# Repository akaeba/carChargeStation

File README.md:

# carChargeStation
Charging station for Faller cars (Li-ion/NiMH)

## Ideas
* use [MCP1631V](https://www.microchip.com/wwwproducts/en/MCP1631V)

## References

### Datasheet
* [MCP1631V](http://ww1.microchip.com/downloads/en/DeviceDoc/22063b.pdf)

### User Guides
* [MCP1631HV Digitally Controlled Programmable Current Source Reference Design](http://ww1.microchip.com/downloads/en/DeviceDoc/51798a.pdf)

### Eval Boards
* [MCP1631RD-DCPC1](https://www.microchip.com/DevelopmentTools/ProductDetails/PartNO/MCP1631RD-DCPC1) (MCP1631HV Digitally Controlled Programmable Current Source Reference Design)

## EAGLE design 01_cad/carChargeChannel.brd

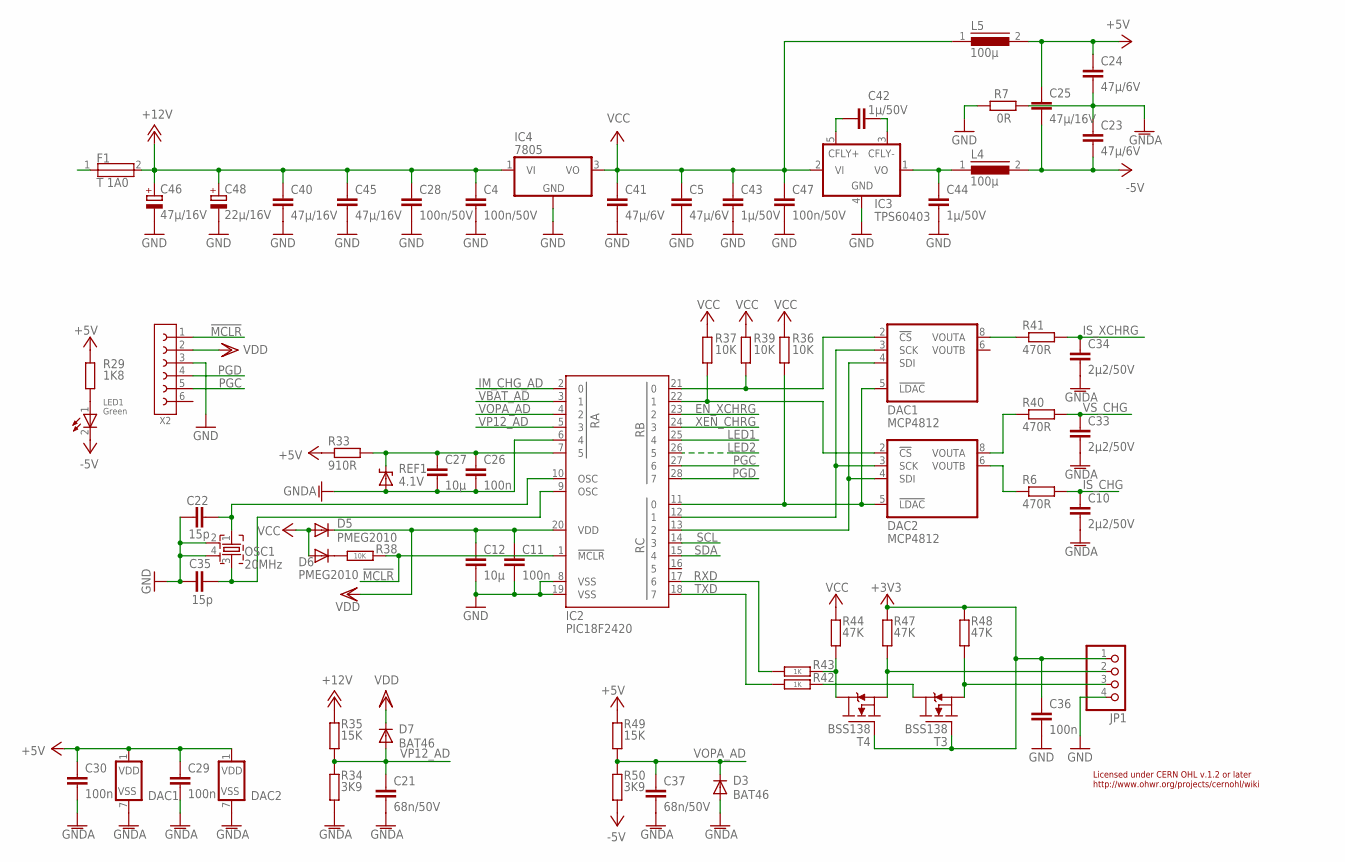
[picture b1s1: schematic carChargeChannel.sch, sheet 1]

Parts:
C4, C28, C47: 100n/50V; 1206
C5, C23, C24, C41: 47µ/6V; 1206
C10, C33, C34: 2µ2/50V; 1206
C11, C26, C29, C30, C36: 100n; 1206
C12, C27: 10µ; 1206
C21, C37: 68n/50V; 1206
C22, C35: 15p; 1206
C25, C40, C45: 47µ/16V; 1210
C42, C43, C44: 1µ/50V; 1206
C46: 47µ/16V; PANC
C48: 22µ/16V; PANB
D3, D7: BAT46; SOD123
D5, D6: PMEG2010; SOD323
DAC1, DAC2: MCP4812; MSOP8
F1: T 1A0; OMT125
IC2: PIC18F2420; SOIC28-7.62
IC3: TPS60403; SOT23-5
IC4: 7805; TO263
JP1: PINHD-1X4; 1X04
L4, L5: 100µ; 1210
LED1: Green; LED3216
OSC1: 20MHz; MT
R6, R40, R41: 470R; 1206
R7: 0R; 1206
R29: 1K8; 1206
R33: 910R; 1206
R34, R50: 3K9; 1206
R35, R49: 15K; 1206
R36, R37, R38, R39: 10K; 1206
R42, R43: 1K; 1206
R44, R47, R48: 47K; 1206
REF1: 4.1V; SOT23
T3, T4: BSS138; SOT23
X2: 2X3; BOXHD-06-2.54-S

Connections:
!CS_DAC1: DAC1.2 (!CS), IC2.21 (0), R39.1
!CS_DAC2: DAC2.2 (!CS), IC2.22 (1), R37.1
!MCLR: IC2.1 (!MCLR), R38.1, X2.1
+3V3: C36.1, JP1.1, R47.2, R48.2, T3.1 (G), T4.1 (G)
+5V: C24.1, C25.1, C29.1, C30.1, DAC1.1 (VDD), DAC2.1 (VDD), L5.2, R29.2, R33.1, R49.2; also elsewhere on the board
+12V: C4.1, C28.1, C40.1, C45.1, C46.CP (+), C48.CP (+), F1.2, IC4.1 (VI), R35.2; also elsewhere on the board
-5V: C23.2, C25.2, L4.2, LED1.2 (C), R50.1; also elsewhere on the board
EN_XCHRG: IC2.23 (2); also elsewhere on the board
GND: C4.2, C5.2, C11.2, C12.2, C22.2, C28.2, C35.2, C36.2, C40.2, C41.2, C43.2, C44.2, C45.2, C46.CN (-), C47.2, C48.CN (-), IC2.8 (VSS), IC2.19 (VSS), IC3.4 (GND), IC4.4 (GND), JP1.4, OSC1.2, OSC1.4, R7.1, X2.3; also elsewhere on the board
GNDA: C10.2, C21.2, C23.1, C24.2, C26.2, C27.2, C29.2, C30.2, C33.2, C34.2, C37.2, D3.A, DAC1.7 (VSS), DAC2.7 (VSS), IC2.6 (4), R7.2, R34.1, REF1.1 (A); also elsewhere on the board
IM_CHG_AD: IC2.2 (0); also elsewhere on the board
IS_CHG: C10.1, R6.2; also elsewhere on the board
IS_XCHRG: C34.1, R41.2; also elsewhere on the board
LED1: IC2.25 (4); also elsewhere on the board
LED2: IC2.26 (5); also elsewhere on the board
unnamed: DAC1.4 (SDI), DAC2.4 (SDI), IC2.13 (2)
unnamed: DAC1.3 (SCK), DAC2.3 (SCK), IC2.12 (1)
unnamed: C42.2, IC3.3 (CFLY-)
unnamed: C42.1, IC3.5 (CFLY+)
unnamed: DAC2.6 (VOUTB), R6.1
unnamed: DAC2.8 (VOUTA), R40.1
unnamed: DAC1.8 (VOUTA), R41.1
unnamed: C44.1, IC3.1 (VO), L4.1
unnamed: C35.1, IC2.9 (OSC), OSC1.3
unnamed: C22.1, IC2.10 (OSC), OSC1.1
unnamed: LED1.1 (A), R29.1
unnamed: DAC1.5 (!LDAC), DAC2.5 (!LDAC), IC2.11 (0), R36.1
unnamed: D6.C, R38.2
unnamed: JP1.3, R48.1, T3.2 (S)
unnamed: JP1.2, R47.1, T4.2 (S)
unnamed: R42.1, T3.3 (D)
unnamed: R43.1, R44.1, T4.3 (D)
PGC: IC2.27 (6), X2.5
PGD: IC2.28 (7), X2.4
RXD: IC2.17 (6), R43.2
SCL: IC2.14 (3)
SDA: IC2.15 (4)
TXD: IC2.18 (7), R42.2
VBAT_AD: IC2.3 (1); also elsewhere on the board
VCC: C5.1, C41.1, C43.1, C47.1, D5.A, D6.A, IC3.2 (VI), IC4.3 (VO), L5.1, R36.2, R37.2, R39.2, R44.2
VDD: C11.1, C12.1, D5.C, D7.C, IC2.20 (VDD), X2.2
VOPA_AD: C37.1, D3.C, IC2.4 (2), R49.1, R50.2
VP12_AD: C21.1, D7.A, IC2.5 (3), R34.2, R35.1
VREF_ADC: C26.1, C27.1, IC2.7 (5), R33.2, REF1.2 (C)
VS_CHG: C33.1, R40.2; also elsewhere on the board
XEN_CHRG: IC2.24 (3); also elsewhere on the board

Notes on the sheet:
Licensed under CERN OHL v.1.2 or later http://www.ohwr.org/projects/cernohl/wiki

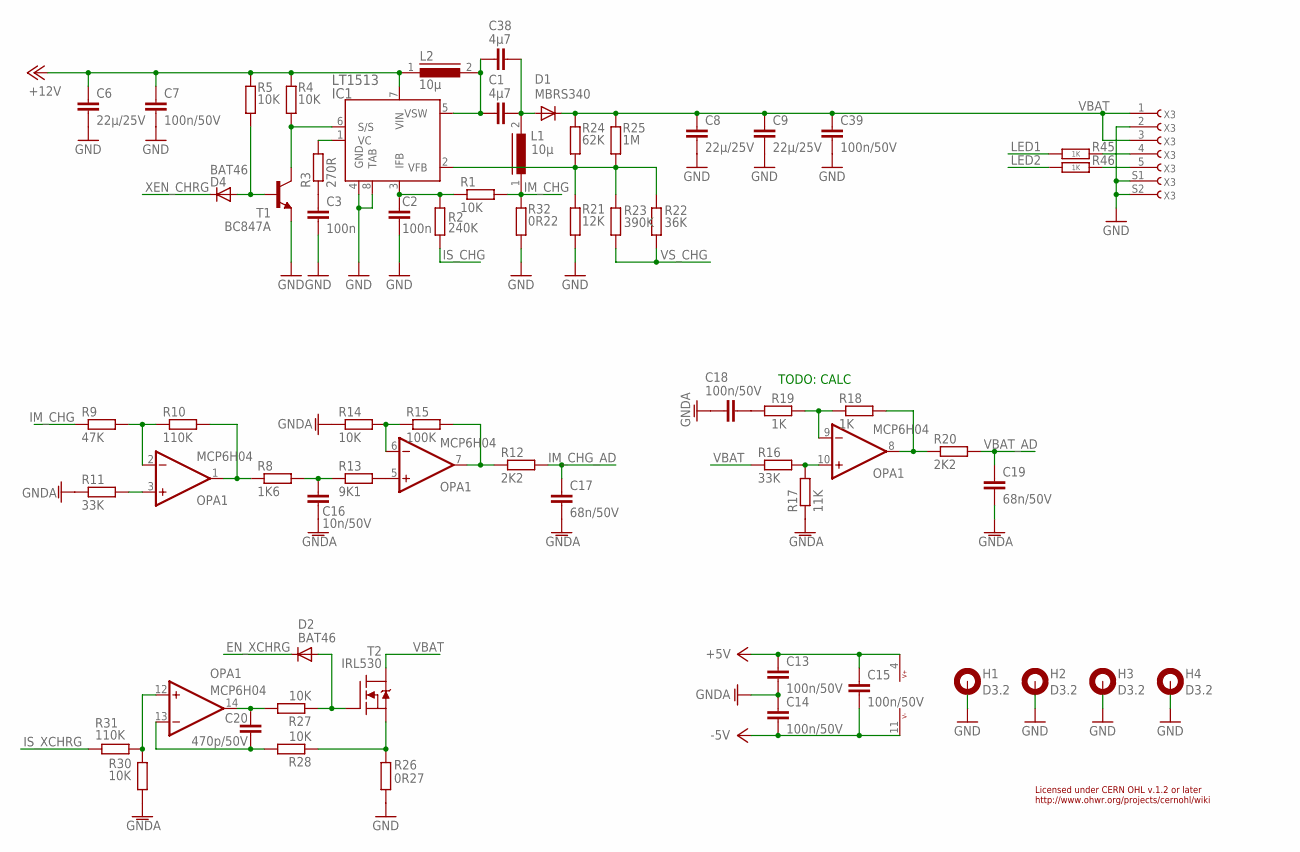
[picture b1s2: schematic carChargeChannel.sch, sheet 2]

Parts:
C1, C38: 4µ7; 1206
C2, C3: 100n; 1206
C6, C8, C9: 22µ/25V; 1210
C7, C13, C14, C15, C18, C39: 100n/50V; 1206
C16: 10n/50V; 1206
C17, C19: 68n/50V; 1206
C20: 470p/50V; 1206
D1: MBRS340; DO214AB
D2, D4: BAT46; SOD123
H1, H2, H3, H4: D3.2; 3,2-PAD
IC1: LT1513; TO263-7
L1, L2: 10µ; DR74
OPA1: MCP6H04; SOIC14
R1, R4, R5, R14, R27, R28, R30: 10K; 1206
R2: 240K; 1206
R3: 270R; 1206
R8: 1K6; 1206
R9: 47K; 1206
R10, R31: 110K; 1206
R11, R16: 33K; 1206
R12, R20: 2K2; 1206
R13: 9K1; 1206
R15: 100K; 1206
R17: 11K; 1206
R18, R19, R45, R46: 1K; 1206
R21: 12K; 1206
R22: 36K; 1206
R23: 390K; 1206
R24: 62K; 1206
R25: 1M; 1206
R26: 0R27; 1206
R32: 0R22; 1206
T1: BC847A; SOT23
T2: IRL530; TO263AB
X3: DIN5; DIN5P

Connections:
+5V: C13.1, C15.1, OPA1.4 (V+); also elsewhere on the board
+12V: C6.1, C7.1, IC1.7 (VIN), L2.1, R4.2, R5.2; also elsewhere on the board
-5V: C14.2, C15.2, OPA1.11 (V-); also elsewhere on the board
EN_XCHRG: D2.C; also elsewhere on the board
GND: C2.2, C3.2, C6.2, C7.2, C8.2, C9.2, C39.2, H1.B3,2, H2.B3,2, H3.B3,2, H4.B3,2, IC1.4 (GND), IC1.8 (TAB), R21.1, R26.1, R32.1, T1.2 (E), X3.2, X3.S1, X3.S2; also elsewhere on the board
GNDA: C13.2, C14.1, C16.2, C17.2, C18.1, C19.2, R11.1, R14.1, R17.1, R30.1; also elsewhere on the board
IM_CHG: L1.1, R1.2, R9.1, R32.2
IM_CHG_AD: C17.1, R12.2; also elsewhere on the board
IS_CHG: R2.1; also elsewhere on the board
IS_XCHRG: R31.1; also elsewhere on the board
LED1: R45.2; also elsewhere on the board
LED2: R46.2; also elsewhere on the board
unnamed: C1.2, C38.2, D1.A, L1.2
unnamed: C1.1, C38.1, IC1.5 (VSW), L2.2
unnamed: OPA1.3 (+IN), R11.2
unnamed: OPA1.8 (OUT), R18.2, R20.1
unnamed: D4.A, R5.1, T1.1 (B)
unnamed: C3.1, R3.1
unnamed: IC1.1 (VC), R3.2
unnamed: C2.1, IC1.3 (IFB), R1.1, R2.2
unnamed: IC1.6 (S/S), R4.1, T1.3 (C)
unnamed: OPA1.2 (-IN), R9.2, R10.1
unnamed: OPA1.1 (OUT), R8.1, R10.2
unnamed: C16.1, R8.2, R13.1
unnamed: OPA1.5 (+IN), R13.2
unnamed: OPA1.6 (-IN), R14.2, R15.1
unnamed: OPA1.10 (+IN), R16.2, R17.2
unnamed: OPA1.7 (OUT), R12.1, R15.2
unnamed: OPA1.9 (-IN), R18.1, R19.2
unnamed: C18.2, R19.1
unnamed: C20.1, OPA1.14 (OUT), R27.2
unnamed: D2.A, R27.1, T2.1 (G)
unnamed: OPA1.12 (+IN), R30.2, R31.2
unnamed: C20.2, OPA1.13 (-IN), R28.2
unnamed: R26.2, R28.1, T2.3 (S)
unnamed: IC1.2 (VFB), R21.2, R22.2, R23.2, R24.1, R25.1
unnamed: R45.1, X3.4
unnamed: R46.1, X3.5
VBAT: C8.1, C9.1, C39.1, D1.C, R16.1, R24.2, R25.2, T2.4 (D), X3.1, X3.3
VBAT_AD: C19.1, R20.2; also elsewhere on the board
VS_CHG: R22.1, R23.1; also elsewhere on the board
XEN_CHRG: D4.C; also elsewhere on the board

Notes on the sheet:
Licensed under CERN OHL v.1.2 or later http://www.ohwr.org/projects/cernohl/wiki
TODO: CALC

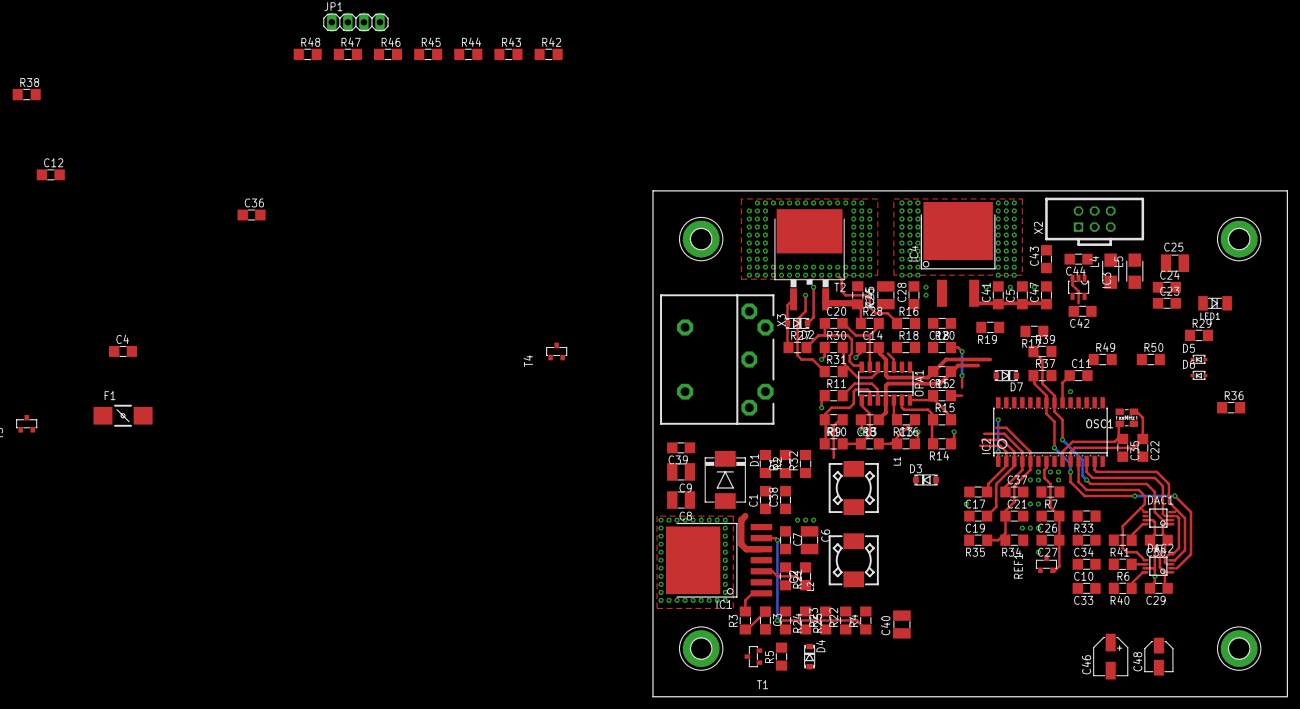
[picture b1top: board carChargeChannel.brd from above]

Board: 2 copper layers, 100.3 x 80.0 mm, 129 parts (0 on the bottom side), 72 nets.

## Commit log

2019-10-10 add gitignore
2019-10-10 add some recherche
2019-10-10 add info
2019-10-11 draft charger model naked
2019-10-11 changed to single winding inductor
2019-10-27 MCP6H01 spice model -> SRC: http://ww1.microchip.com/downloads/en/DeviceDoc/MCP6H01_MM_B.zip
2019-10-27 current sensor amp -> intermediate commit
2019-10-27 intermediate
2019-10-27 finished current sense model
2019-11-01 moved spice model
2019-11-01 restruct
2019-11-01 irl530.lib -> SRC: http://www.vishay.com/docs/90598/sihl530.lib
2020-03-22 add TPS60403 for pwr supply
2020-04-09 intermediate4
2020-04-09 update git ignore
2020-04-09 start of layout
2020-04-10 ongoing...
2020-05-10 ongoging

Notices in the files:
parts and their libraries:
omcCapacitor: Copyright & License
This library is licensed under the General Public License, Version 2.
More Information about the General Public License is available at http://www.gnu.org/copyleft/gpl.html.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
omcDiode: This library is licensed under the General Public License, Version 3.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
